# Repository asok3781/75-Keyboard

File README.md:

# Asok75
A 75% keyboard PCB.

A simple [acrylic case](Case) has also been designed - .dxf files are in the Case folder in the repository.

This PCB is designed to work with [QMK firmware](https://github.com/asok3781/qmk_firmware/tree/asok/keyboards/asok/asok75) (firmware is in my branch of the QMK firmware in the expected location).

A [VIA definition](asok75VIAdefinition) has also been created to be able to customise the layout of the keyboard easily.

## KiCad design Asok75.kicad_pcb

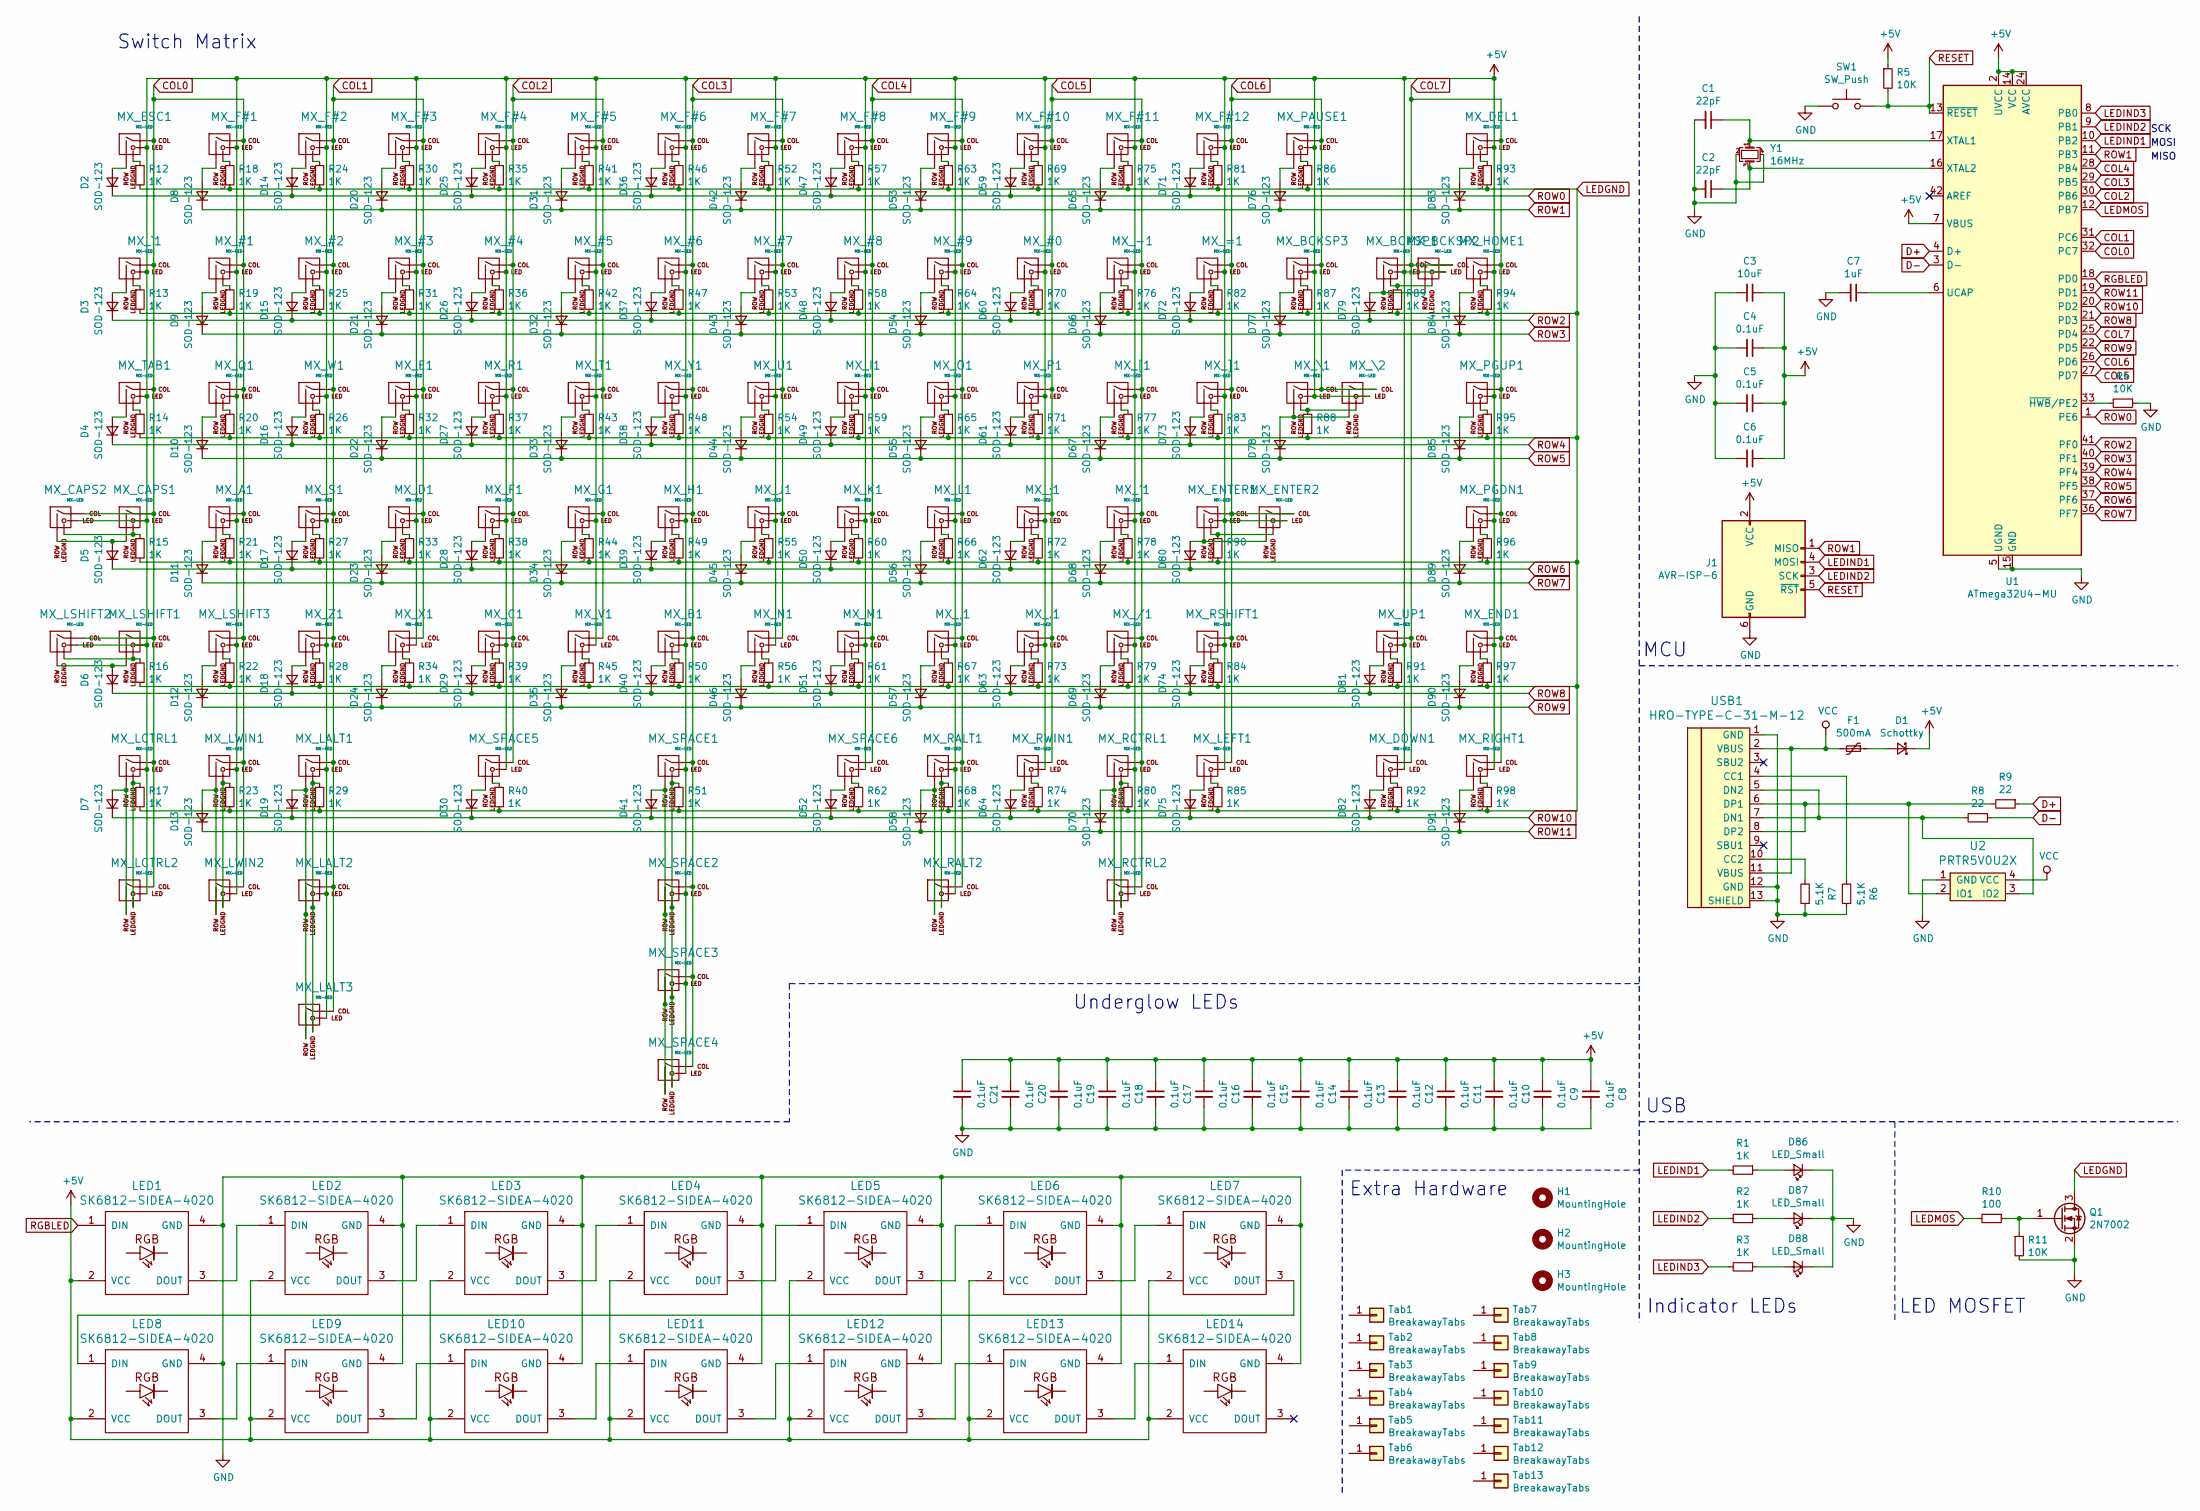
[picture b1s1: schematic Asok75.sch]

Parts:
C1, C2: 22pF; C_0805_2012Metric
C3: 10uF; C_0805_2012Metric
C4, C5, C6, C8, C9, C10, C11, C12, C13, C14, C15, C16, C17, C18, C19, C20, C21: 0.1uF; C_0805_2012Metric
C7: 1uF; C_0805_2012Metric
D1: Schottky; D_SOD-123-Pretty
D2, D3, D4, D5, D6, D7, D8, D9, D10, D11, D12, D13, D14, D15, D16, D17, D18, D19, D20, D21, D22, D23, D24, D25, D26, D27, D28, D29, D30, D31, D32, D33, D34, D35, D36, D37, D38, D39, D40, D41, D42, D43, D44, D45, D46, D47, D48, D49, D50, D51, D52, D53, D54, D55, D56, D57, D58, D59, D60, D61, D62, D63, D64, D65, D66, D67, D68, D69, D70, D71, D72, D73, D74, D75, D76, D77, D78, D79, D80, D81, D82, D83, D84, D85, D89, D90, D91: SOD-123; D_SOD-123-Pretty
D86, D87, D88: LED_Small; LED_D3.0mm-Pretty
F1: 500mA; Fuse_1206_3216Metric
H1, H2, H3: MountingHole; mounting
J1: AVR-ISP-6; Reset_Pretty-Mask
LED1, LED2, LED3, LED4, LED5, LED6, LED7, LED8, LED9, LED10, LED11, LED12, LED13, LED14: SK6812-SIDEA-4020
MX_#0, MX_#1, MX_#2, MX_#3, MX_#4, MX_#5, MX_#6, MX_#7, MX_#8, MX_#9: MX-LED; MXOnly-1U
MX_'1: MX-LED; MXOnly-1U
MX_,1: MX-LED; MXOnly-1U
MX_-1: MX-LED; MXOnly-1U
MX_.1: MX-LED; MXOnly-1U
MX_/1: MX-LED; MXOnly-1U
MX_;1: MX-LED; MXOnly-1U
MX_=1: MX-LED; MXOnly-1U
MX_A1: MX-LED; MXOnly-1U
MX_B1: MX-LED; MXOnly-1U
MX_BCKSP1: MX-LED; MXOnly-2U
MX_BCKSP2, MX_BCKSP3: MX-LED; MXOnly-1U
MX_C1: MX-LED; MXOnly-1U
MX_CAPS1: MX-LED; MXOnly-1.75U
MX_CAPS2: MX-LED; MXOnly-1.25U
MX_D1: MX-LED; MXOnly-1U
MX_DEL1: MX-LED; MXOnly-1U
MX_DOWN1: MX-LED; MXOnly-1U
MX_E1: MX-LED; MXOnly-1U
MX_END1: MX-LED; MXOnly-1U
MX_ENTER1: MX-LED; MXOnly-2.25U-ReversedStabilizers
MX_ENTER2: MX-LED; MXOnly-ISO-ROTATED-ReversedStabilizers
MX_ESC1: MX-LED; MXOnly-1U
MX_F1: MX-LED; MXOnly-1U
MX_F#1, MX_F#2, MX_F#3, MX_F#4, MX_F#5, MX_F#6, MX_F#7, MX_F#8, MX_F#9, MX_F#10, MX_F#11, MX_F#12: MX-LED; MXOnly-1U
MX_G1: MX-LED; MXOnly-1U
MX_H1: MX-LED; MXOnly-1U
MX_HOME1: MX-LED; MXOnly-1U
MX_I1: MX-LED; MXOnly-1U
MX_J1: MX-LED; MXOnly-1U
MX_K1: MX-LED; MXOnly-1U
MX_L1: MX-LED; MXOnly-1U
MX_LALT1: MX-LED; MXOnly-1.25U
MX_LALT2: MX-LED; MXOnly-1.5U-FLIPPED
MX_LALT3: MX-LED; MXOnly-1.5U
MX_LCTRL1: MX-LED; MXOnly-1.25U
MX_LCTRL2: MX-LED; MXOnly-1.5U-FLIPPED
MX_LEFT1: MX-LED; MXOnly-1U
MX_LSHIFT1: MX-LED; MXOnly-2.25U
MX_LSHIFT2: MX-LED; MXOnly-1.25U
MX_LSHIFT3: MX-LED; MXOnly-1U
MX_LWIN1: MX-LED; MXOnly-1.25U
MX_LWIN2: MX-LED; MXOnly-1U-FLIPPED
MX_M1: MX-LED; MXOnly-1U
MX_N1: MX-LED; MXOnly-1U
MX_O1: MX-LED; MXOnly-1U
MX_P1: MX-LED; MXOnly-1U
MX_PAUSE1: MX-LED; MXOnly-1U
MX_PGDN1: MX-LED; MXOnly-1U
MX_PGUP1: MX-LED; MXOnly-1U
MX_Q1: MX-LED; MXOnly-1U
MX_R1: MX-LED; MXOnly-1U
MX_RALT1: MX-LED; MXOnly-1U
MX_RALT2: MX-LED; MXOnly-1.5U
MX_RCTRL1: MX-LED; MXOnly-1U
MX_RCTRL2: MX-LED; MXOnly-1.5U
MX_RIGHT1: MX-LED; MXOnly-1U
MX_RSHIFT1: MX-LED; MXOnly-1.75U
MX_RWIN1: MX-LED; MXOnly-1U
MX_S1: MX-LED; MXOnly-1U
MX_SPACE1: MX-LED; MXOnly-6.25U-ReversedStabilizers
MX_SPACE2, MX_SPACE3: MX-LED; MXOnly-7U-ReversedStabilizers
MX_SPACE4: MX-LED; MXOnly-1.25U
MX_SPACE5: MX-LED; MXOnly-2.75U-ReversedStabilizers
MX_SPACE6: MX-LED; MXOnly-2.25U-ReversedStabilizers
MX_T1: MX-LED; MXOnly-1U
MX_TAB1: MX-LED; MXOnly-1.5U
MX_U1: MX-LED; MXOnly-1U
MX_UP1: MX-LED; MXOnly-1U
MX_V1: MX-LED; MXOnly-1U
MX_W1: MX-LED; MXOnly-1U
MX_X1: MX-LED; MXOnly-1U
MX_Y1: MX-LED; MXOnly-1U
MX_Z1: MX-LED; MXOnly-1U
MX_[1: MX-LED; MXOnly-1U
MX_\1: MX-LED; MXOnly-1.5U
MX_\2: MX-LED; MXOnly-1U
MX_]1: MX-LED; MXOnly-1U
MX_`1: MX-LED; MXOnly-1U
Q1: 2N7002; SOT-23
R1, R2, R3, R12, R13, R14, R15, R16, R17, R18, R19, R20, R21, R22, R23, R24, R25, R26, R27, R28, R29, R30, R31, R32, R33, R34, R35, R36, R37, R38, R39, R40, R41, R42, R43, R44, R45, R46, R47, R48, R49, R50, R51, R52, R53, R54, R55, R56, R57, R58, R59, R60, R61, R62, R63, R64, R65, R66, R67, R68, R69, R70, R71, R72, R73, R74, R75, R76, R77, R78, R79, R80, R81, R82, R83, R84, R85, R86, R87, R88, R89, R90, R91, R92, R93, R94, R95, R96, R97, R98: 1K; R_0805_2012Metric
R4, R5, R11: 10K; R_0805_2012Metric
R6, R7: 5.1K; R_0805_2012Metric
R8, R9: 22; R_0805_2012Metric
R10: 100; R_0805_2012Metric
SW1: SW_Push; SKQG-1155865
Tab1, Tab2, Tab3, Tab4, Tab5, Tab6, Tab7, Tab8, Tab9, Tab10, Tab11, Tab12, Tab13: BreakawayTabs; breakaway-mousebites
U1: ATmega32U4-MU; QFN-44-1EP_7x7mm_P0.5mm_EP5.2x5.2mm
U2: PRTR5V0U2X; SOT143B
USB1: HRO-TYPE-C-31-M-12; HRO-TYPE-C-31-M-12-Assembly
Y1: 16MHz; Crystal_SMD_3225-4Pin_3.2x2.5mm

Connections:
+5V: C3.1, C4.1, C5.1, C6.1, C8.1, C9.1, C10.1, C11.1, C12.1, C13.1, C14.1, C15.1, C16.1, C17.1, C18.1, C19.1, C20.1, C21.1, D1.1 (K), J1.2 (VCC), LED1.2 (VCC), LED2.2 (VCC), LED3.2 (VCC), LED4.2 (VCC), LED5.2 (VCC), LED6.2 (VCC), LED7.2 (VCC), LED8.2 (VCC), LED9.2 (VCC), LED10.2 (VCC), LED11.2 (VCC), LED12.2 (VCC), LED13.2 (VCC), LED14.2 (VCC), MX_#0.3 (LED), MX_#1.3 (LED), MX_#2.3 (LED), MX_#3.3 (LED), MX_#4.3 (LED), MX_#5.3 (LED), MX_#6.3 (LED), MX_#7.3 (LED), MX_#8.3 (LED), MX_#9.3 (LED), MX_'1.3 (LED), MX_,1.3 (LED), MX_-1.3 (LED), MX_.1.3 (LED), MX_/1.3 (LED), MX_;1.3 (LED), MX_=1.3 (LED), MX_A1.3 (LED), MX_B1.3 (LED), MX_BCKSP1.3 (LED), MX_BCKSP2.3 (LED), MX_BCKSP3.3 (LED), MX_C1.3 (LED), MX_CAPS1.3 (LED), MX_CAPS2.3 (LED), MX_D1.3 (LED), MX_DEL1.3 (LED), MX_DOWN1.3 (LED), MX_E1.3 (LED), MX_END1.3 (LED), MX_ENTER1.3 (LED), MX_ENTER2.3 (LED), MX_ESC1.3 (LED), MX_F1.3 (LED), MX_F#1.3 (LED), MX_F#2.3 (LED), MX_F#3.3 (LED), MX_F#4.3 (LED), MX_F#5.3 (LED), MX_F#6.3 (LED), MX_F#7.3 (LED), MX_F#8.3 (LED), MX_F#9.3 (LED), MX_F#10.3 (LED), MX_F#11.3 (LED), MX_F#12.3 (LED), MX_G1.3 (LED), MX_H1.3 (LED), MX_HOME1.3 (LED), MX_I1.3 (LED), MX_J1.3 (LED), MX_K1.3 (LED), MX_L1.3 (LED), MX_LALT1.3 (LED), MX_LALT2.3 (LED), MX_LALT3.3 (LED), MX_LCTRL1.3 (LED), MX_LCTRL2.3 (LED), MX_LEFT1.3 (LED), MX_LSHIFT1.3 (LED), MX_LSHIFT2.3 (LED), MX_LSHIFT3.3 (LED), MX_LWIN1.3 (LED), MX_LWIN2.3 (LED), MX_M1.3 (LED), MX_N1.3 (LED), MX_O1.3 (LED), MX_P1.3 (LED), MX_PAUSE1.3 (LED), MX_PGDN1.3 (LED), MX_PGUP1.3 (LED), MX_Q1.3 (LED), MX_R1.3 (LED), MX_RALT1.3 (LED), MX_RALT2.3 (LED), MX_RCTRL1.3 (LED), MX_RCTRL2.3 (LED), MX_RIGHT1.3 (LED), MX_RSHIFT1.3 (LED), MX_RWIN1.3 (LED), MX_S1.3 (LED), MX_SPACE1.3 (LED), MX_SPACE2.3 (LED), MX_SPACE3.3 (LED), MX_SPACE4.3 (LED), MX_SPACE5.3 (LED), MX_SPACE6.3 (LED), MX_T1.3 (LED), MX_TAB1.3 (LED), MX_U1.3 (LED), MX_UP1.3 (LED), MX_V1.3 (LED), MX_W1.3 (LED), MX_X1.3 (LED), MX_Y1.3 (LED), MX_Z1.3 (LED), MX_[1.3 (LED), MX_\1.3 (LED), MX_\2.3 (LED), MX_]1.3 (LED), MX_`1.3 (LED), R5.1, U1.2 (UVCC), U1.7 (VBUS), U1.14 (VCC), U1.24 (AVCC), U1.34 (VCC), U1.44 (AVCC); also elsewhere on the board
COL0: MX_#1.1 (COL), MX_A1.1 (COL), MX_CAPS1.1 (COL), MX_CAPS2.1 (COL), MX_ESC1.1 (COL), MX_F#1.1 (COL), MX_LCTRL1.1 (COL), MX_LCTRL2.1 (COL), MX_LSHIFT1.1 (COL), MX_LSHIFT2.1 (COL), MX_LSHIFT3.1 (COL), MX_LWIN1.1 (COL), MX_LWIN2.1 (COL), MX_Q1.1 (COL), MX_TAB1.1 (COL), MX_`1.1 (COL), U1.32 (PC7)
COL1: MX_#2.1 (COL), MX_#3.1 (COL), MX_D1.1 (COL), MX_E1.1 (COL), MX_F#2.1 (COL), MX_F#3.1 (COL), MX_LALT1.1 (COL), MX_LALT2.1 (COL), MX_LALT3.1 (COL), MX_S1.1 (COL), MX_W1.1 (COL), MX_X1.1 (COL), MX_Z1.1 (COL), U1.31 (PC6)
COL2: MX_#4.1 (COL), MX_#5.1 (COL), MX_C1.1 (COL), MX_F1.1 (COL), MX_F#4.1 (COL), MX_F#5.1 (COL), MX_G1.1 (COL), MX_R1.1 (COL), MX_SPACE5.1 (COL), MX_T1.1 (COL), MX_V1.1 (COL), U1.30 (PB6)
COL3: MX_#6.1 (COL), MX_#7.1 (COL), MX_B1.1 (COL), MX_F#6.1 (COL), MX_F#7.1 (COL), MX_H1.1 (COL), MX_J1.1 (COL), MX_N1.1 (COL), MX_SPACE1.1 (COL), MX_SPACE2.1 (COL), MX_SPACE3.1 (COL), MX_SPACE4.1 (COL), MX_U1.1 (COL), MX_Y1.1 (COL), U1.29 (PB5)
COL4: MX_#8.1 (COL), MX_#9.1 (COL), MX_,1.1 (COL), MX_F#8.1 (COL), MX_F#9.1 (COL), MX_I1.1 (COL), MX_K1.1 (COL), MX_L1.1 (COL), MX_M1.1 (COL), MX_O1.1 (COL), MX_RALT1.1 (COL), MX_RALT2.1 (COL), MX_SPACE6.1 (COL), U1.28 (PB4)
COL5: MX_#0.1 (COL), MX_'1.1 (COL), MX_-1.1 (COL), MX_.1.1 (COL), MX_/1.1 (COL), MX_;1.1 (COL), MX_F#10.1 (COL), MX_F#11.1 (COL), MX_P1.1 (COL), MX_RCTRL1.1 (COL), MX_RCTRL2.1 (COL), MX_RWIN1.1 (COL), MX_[1.1 (COL), U1.27 (PD7)
COL6: MX_=1.1 (COL), MX_BCKSP3.1 (COL), MX_ENTER1.1 (COL), MX_ENTER2.1 (COL), MX_F#12.1 (COL), MX_LEFT1.1 (COL), MX_PAUSE1.1 (COL), MX_RSHIFT1.1 (COL), MX_\1.1 (COL), MX_\2.1 (COL), MX_]1.1 (COL), U1.26 (PD6)
COL7: MX_BCKSP1.1 (COL), MX_BCKSP2.1 (COL), MX_DEL1.1 (COL), MX_DOWN1.1 (COL), MX_END1.1 (COL), MX_HOME1.1 (COL), MX_PGDN1.1 (COL), MX_PGUP1.1 (COL), MX_RIGHT1.1 (COL), MX_UP1.1 (COL), U1.25 (PD4)
D+: R9.1, U1.4 (D+)
D-: R8.1, U1.3 (D-)
GND: C1.2, C2.2, C3.2, C4.2, C5.2, C6.2, C7.2, C8.2, C9.2, C10.2, C11.2, C12.2, C13.2, C14.2, C15.2, C16.2, C17.2, C18.2, C19.2, C20.2, C21.2, D86.1 (K), D87.1 (K), D88.1 (K), J1.6 (GND), LED1.4 (GND), LED2.4 (GND), LED3.4 (GND), LED4.4 (GND), LED5.4 (GND), LED6.4 (GND), LED7.4 (GND), LED8.4 (GND), LED9.4 (GND), LED10.4 (GND), LED11.4 (GND), LED12.4 (GND), LED13.4 (GND), LED14.4 (GND), Q1.2 (S), R4.1, R6.1, R7.1, R11.2, SW1.1, U1.5 (UGND), U1.15 (GND), U1.23 (GND), U1.35 (GND), U1.43 (GND), U1.45 (GND), U2.1 (GND), USB1.1 (GND), USB1.12 (GND), USB1.13 (SHIELD), Y1.2, Y1.4; also elsewhere on the board
LEDGND: Q1.3 (D), R12.2, R13.2, R14.2, R15.2, R16.2, R17.2, R18.2, R19.2, R20.2, R21.2, R22.2, R23.2, R24.2, R25.2, R26.2, R27.2, R28.2, R29.2, R30.2, R31.2, R32.2, R33.2, R34.2, R35.2, R36.2, R37.2, R38.2, R39.2, R40.2, R41.2, R42.2, R43.2, R44.2, R45.2, R46.2, R47.2, R48.2, R49.2, R50.2, R51.2, R52.2, R53.2, R54.2, R55.2, R56.2, R57.2, R58.2, R59.2, R60.2, R61.2, R62.2, R63.2, R64.2, R65.2, R66.2, R67.2, R68.2, R69.2, R70.2, R71.2, R72.2, R73.2, R74.2, R75.2, R76.2, R77.2, R78.2, R79.2, R80.2, R81.2, R82.2, R83.2, R84.2, R85.2, R86.2, R87.2, R88.2, R89.2, R90.2, R91.2, R92.2, R93.2, R94.2, R95.2, R96.2, R97.2, R98.2
LEDIND1: J1.4 (MOSI), R1.2, U1.10 (PB2)
LEDIND2: J1.3 (SCK), R2.2, U1.9 (PB1)
LEDIND3: R3.2, U1.8 (PB0)
LEDMOS: R10.2, U1.12 (PB7)
unnamed: C1.1, U1.17 (XTAL1), Y1.1
unnamed: C2.1, U1.16 (XTAL2), Y1.3
unnamed: C7.1, U1.6 (UCAP)
unnamed: D1.2 (A), F1.1
unnamed: D2.2 (A), MX_ESC1.2 (ROW)
unnamed: D3.2 (A), MX_`1.2 (ROW)
unnamed: D4.2 (A), MX_TAB1.2 (ROW)
unnamed: D5.2 (A), MX_CAPS1.2 (ROW), MX_CAPS2.2 (ROW)
unnamed: D6.2 (A), MX_LSHIFT1.2 (ROW), MX_LSHIFT2.2 (ROW)
unnamed: D7.2 (A), MX_LCTRL1.2 (ROW), MX_LCTRL2.2 (ROW)
unnamed: D8.2 (A), MX_F#1.2 (ROW)
unnamed: D9.2 (A), MX_#1.2 (ROW)
unnamed: D10.2 (A), MX_Q1.2 (ROW)
unnamed: D11.2 (A), MX_A1.2 (ROW)
unnamed: D12.2 (A), MX_LSHIFT3.2 (ROW)
unnamed: D13.2 (A), MX_LWIN1.2 (ROW), MX_LWIN2.2 (ROW)
unnamed: D14.2 (A), MX_F#2.2 (ROW)
unnamed: D15.2 (A), MX_#2.2 (ROW)
unnamed: D16.2 (A), MX_W1.2 (ROW)
unnamed: D17.2 (A), MX_S1.2 (ROW)
unnamed: D18.2 (A), MX_Z1.2 (ROW)
unnamed: D19.2 (A), MX_LALT1.2 (ROW), MX_LALT2.2 (ROW), MX_LALT3.2 (ROW)
unnamed: D20.2 (A), MX_F#3.2 (ROW)
unnamed: D21.2 (A), MX_#3.2 (ROW)
unnamed: D22.2 (A), MX_E1.2 (ROW)
unnamed: D23.2 (A), MX_D1.2 (ROW)
unnamed: D24.2 (A), MX_X1.2 (ROW)
unnamed: D25.2 (A), MX_F#4.2 (ROW)
unnamed: D26.2 (A), MX_#4.2 (ROW)
unnamed: D27.2 (A), MX_R1.2 (ROW)
unnamed: D28.2 (A), MX_F1.2 (ROW)
unnamed: D29.2 (A), MX_C1.2 (ROW)
unnamed: D30.2 (A), MX_SPACE5.2 (ROW)
unnamed: D31.2 (A), MX_F#5.2 (ROW)
unnamed: D32.2 (A), MX_#5.2 (ROW)
unnamed: D33.2 (A), MX_T1.2 (ROW)
unnamed: D34.2 (A), MX_G1.2 (ROW)
unnamed: D35.2 (A), MX_V1.2 (ROW)
unnamed: D36.2 (A), MX_F#6.2 (ROW)
unnamed: D37.2 (A), MX_#6.2 (ROW)
unnamed: D38.2 (A), MX_Y1.2 (ROW)
unnamed: D39.2 (A), MX_H1.2 (ROW)
unnamed: D40.2 (A), MX_B1.2 (ROW)
unnamed: D41.2 (A), MX_SPACE1.2 (ROW), MX_SPACE2.2 (ROW), MX_SPACE3.2 (ROW), MX_SPACE4.2 (ROW)
unnamed: D42.2 (A), MX_F#7.2 (ROW)
unnamed: D43.2 (A), MX_#7.2 (ROW)
unnamed: D44.2 (A), MX_U1.2 (ROW)
unnamed: D45.2 (A), MX_J1.2 (ROW)
unnamed: D46.2 (A), MX_N1.2 (ROW)
unnamed: D47.2 (A), MX_F#8.2 (ROW)
unnamed: D48.2 (A), MX_#8.2 (ROW)
unnamed: D49.2 (A), MX_I1.2 (ROW)
unnamed: D50.2 (A), MX_K1.2 (ROW)
unnamed: D51.2 (A), MX_M1.2 (ROW)
unnamed: D52.2 (A), MX_SPACE6.2 (ROW)
unnamed: D53.2 (A), MX_F#9.2 (ROW)
unnamed: D54.2 (A), MX_#9.2 (ROW)
unnamed: D55.2 (A), MX_O1.2 (ROW)
unnamed: D56.2 (A), MX_L1.2 (ROW)
unnamed: D57.2 (A), MX_,1.2 (ROW)
unnamed: D58.2 (A), MX_RALT1.2 (ROW), MX_RALT2.2 (ROW)
unnamed: D59.2 (A), MX_F#10.2 (ROW)
unnamed: D60.2 (A), MX_#0.2 (ROW)
unnamed: D61.2 (A), MX_P1.2 (ROW)
unnamed: D62.2 (A), MX_;1.2 (ROW)
unnamed: D63.2 (A), MX_.1.2 (ROW)
unnamed: D64.2 (A), MX_RWIN1.2 (ROW)
unnamed: D65.2 (A), MX_F#11.2 (ROW)
unnamed: D66.2 (A), MX_-1.2 (ROW)
unnamed: D67.2 (A), MX_[1.2 (ROW)
unnamed: D68.2 (A), MX_'1.2 (ROW)
unnamed: D69.2 (A), MX_/1.2 (ROW)
unnamed: D70.2 (A), MX_RCTRL1.2 (ROW), MX_RCTRL2.2 (ROW)
unnamed: D71.2 (A), MX_F#12.2 (ROW)
unnamed: D72.2 (A), MX_=1.2 (ROW)
unnamed: D73.2 (A), MX_]1.2 (ROW)
unnamed: D74.2 (A), MX_RSHIFT1.2 (ROW)
unnamed: D75.2 (A), MX_LEFT1.2 (ROW)
unnamed: D76.2 (A), MX_PAUSE1.2 (ROW)
unnamed: D77.2 (A), MX_BCKSP3.2 (ROW)
unnamed: D78.2 (A), MX_\1.2 (ROW), MX_\2.2 (ROW)
unnamed: D79.2 (A), MX_BCKSP1.2 (ROW), MX_BCKSP2.2 (ROW)
unnamed: D80.2 (A), MX_ENTER1.2 (ROW), MX_ENTER2.2 (ROW)
unnamed: D81.2 (A), MX_UP1.2 (ROW)
unnamed: D82.2 (A), MX_DOWN1.2 (ROW)
unnamed: D83.2 (A), MX_DEL1.2 (ROW)
unnamed: D84.2 (A), MX_HOME1.2 (ROW)
unnamed: D85.2 (A), MX_PGUP1.2 (ROW)
unnamed: D86.2 (A), R1.1
unnamed: D87.2 (A), R2.1
unnamed: D88.2 (A), R3.1
unnamed: D89.2 (A), MX_PGDN1.2 (ROW)
unnamed: D90.2 (A), MX_END1.2 (ROW)
unnamed: D91.2 (A), MX_RIGHT1.2 (ROW)
unnamed: LED1.3 (DOUT), LED2.1 (DIN)
unnamed: LED2.3 (DOUT), LED3.1 (DIN)
unnamed: LED3.3 (DOUT), LED4.1 (DIN)
unnamed: LED4.3 (DOUT), LED5.1 (DIN)
unnamed: LED5.3 (DOUT), LED6.1 (DIN)
unnamed: LED6.3 (DOUT), LED7.1 (DIN)
unnamed: LED7.3 (DOUT), LED8.1 (DIN)
unnamed: LED8.3 (DOUT), LED9.1 (DIN)
unnamed: LED9.3 (DOUT), LED10.1 (DIN)
unnamed: LED10.3 (DOUT), LED11.1 (DIN)
unnamed: LED11.3 (DOUT), LED12.1 (DIN)
unnamed: LED12.3 (DOUT), LED13.1 (DIN)
unnamed: LED13.3 (DOUT), LED14.1 (DIN)
unnamed: MX_#0.4 (LEDGND), R70.1
unnamed: MX_#1.4 (LEDGND), R19.1
unnamed: MX_#2.4 (LEDGND), R25.1
unnamed: MX_#3.4 (LEDGND), R31.1
unnamed: MX_#4.4 (LEDGND), R36.1
unnamed: MX_#5.4 (LEDGND), R42.1
unnamed: MX_#6.4 (LEDGND), R47.1
unnamed: MX_#7.4 (LEDGND), R53.1
unnamed: MX_#8.4 (LEDGND), R58.1
unnamed: MX_#9.4 (LEDGND), R64.1
unnamed: MX_'1.4 (LEDGND), R78.1
unnamed: MX_,1.4 (LEDGND), R67.1
unnamed: MX_-1.4 (LEDGND), R76.1
unnamed: MX_.1.4 (LEDGND), R73.1
unnamed: MX_/1.4 (LEDGND), R79.1
unnamed: MX_;1.4 (LEDGND), R72.1
unnamed: MX_=1.4 (LEDGND), R82.1
unnamed: MX_A1.4 (LEDGND), R21.1
unnamed: MX_B1.4 (LEDGND), R50.1
unnamed: MX_BCKSP1.4 (LEDGND), MX_BCKSP2.4 (LEDGND), R89.1
unnamed: MX_BCKSP3.4 (LEDGND), R87.1
unnamed: MX_C1.4 (LEDGND), R39.1
unnamed: MX_CAPS1.4 (LEDGND), MX_CAPS2.4 (LEDGND), R15.1
unnamed: MX_D1.4 (LEDGND), R33.1
unnamed: MX_DEL1.4 (LEDGND), R93.1
unnamed: MX_DOWN1.4 (LEDGND), R92.1
unnamed: MX_E1.4 (LEDGND), R32.1
unnamed: MX_END1.4 (LEDGND), R97.1
unnamed: MX_ENTER1.4 (LEDGND), MX_ENTER2.4 (LEDGND), R90.1
unnamed: MX_ESC1.4 (LEDGND), R12.1
unnamed: MX_F1.4 (LEDGND), R38.1
unnamed: MX_F#1.4 (LEDGND), R18.1
unnamed: MX_F#2.4 (LEDGND), R24.1
unnamed: MX_F#3.4 (LEDGND), R30.1
unnamed: MX_F#4.4 (LEDGND), R35.1
unnamed: MX_F#5.4 (LEDGND), R41.1
unnamed: MX_F#6.4 (LEDGND), R46.1
unnamed: MX_F#7.4 (LEDGND), R52.1
unnamed: MX_F#8.4 (LEDGND), R57.1
unnamed: MX_F#9.4 (LEDGND), R63.1
unnamed: MX_F#10.4 (LEDGND), R69.1
unnamed: MX_F#11.4 (LEDGND), R75.1
unnamed: MX_F#12.4 (LEDGND), R81.1
unnamed: MX_G1.4 (LEDGND), R44.1
unnamed: MX_H1.4 (LEDGND), R49.1
unnamed: MX_HOME1.4 (LEDGND), R94.1
unnamed: MX_I1.4 (LEDGND), R59.1
unnamed: MX_J1.4 (LEDGND), R55.1
unnamed: MX_K1.4 (LEDGND), R60.1
unnamed: MX_L1.4 (LEDGND), R66.1
unnamed: MX_LALT1.4 (LEDGND), MX_LALT2.4 (LEDGND), MX_LALT3.4 (LEDGND), R29.1
unnamed: MX_LCTRL1.4 (LEDGND), MX_LCTRL2.4 (LEDGND), R17.1
unnamed: MX_LEFT1.4 (LEDGND), R85.1
unnamed: MX_LSHIFT1.4 (LEDGND), MX_LSHIFT2.4 (LEDGND), R16.1
unnamed: MX_LSHIFT3.4 (LEDGND), R22.1
unnamed: MX_LWIN1.4 (LEDGND), MX_LWIN2.4 (LEDGND), R23.1
unnamed: MX_M1.4 (LEDGND), R61.1
unnamed: MX_N1.4 (LEDGND), R56.1
unnamed: MX_O1.4 (LEDGND), R65.1
unnamed: MX_P1.4 (LEDGND), R71.1
unnamed: MX_PAUSE1.4 (LEDGND), R86.1
unnamed: MX_PGDN1.4 (LEDGND), R96.1
unnamed: MX_PGUP1.4 (LEDGND), R95.1
unnamed: MX_Q1.4 (LEDGND), R20.1
unnamed: MX_R1.4 (LEDGND), R37.1
unnamed: MX_RALT1.4 (LEDGND), MX_RALT2.4 (LEDGND), R68.1
unnamed: MX_RCTRL1.4 (LEDGND), MX_RCTRL2.4 (LEDGND), R80.1
unnamed: MX_RIGHT1.4 (LEDGND), R98.1
unnamed: MX_RSHIFT1.4 (LEDGND), R84.1
unnamed: MX_RWIN1.4 (LEDGND), R74.1
unnamed: MX_S1.4 (LEDGND), R27.1
unnamed: MX_SPACE1.4 (LEDGND), MX_SPACE2.4 (LEDGND), MX_SPACE3.4 (LEDGND), MX_SPACE4.4 (LEDGND), R51.1
unnamed: MX_SPACE5.4 (LEDGND), R40.1
unnamed: MX_SPACE6.4 (LEDGND), R62.1
unnamed: MX_T1.4 (LEDGND), R43.1
unnamed: MX_TAB1.4 (LEDGND), R14.1
unnamed: MX_U1.4 (LEDGND), R54.1
unnamed: MX_UP1.4 (LEDGND), R91.1
unnamed: MX_V1.4 (LEDGND), R45.1
unnamed: MX_W1.4 (LEDGND), R26.1
unnamed: MX_X1.4 (LEDGND), R34.1
unnamed: MX_Y1.4 (LEDGND), R48.1
unnamed: MX_Z1.4 (LEDGND), R28.1
unnamed: MX_[1.4 (LEDGND), R77.1
unnamed: MX_\1.4 (LEDGND), MX_\2.4 (LEDGND), R88.1
unnamed: MX_]1.4 (LEDGND), R83.1
unnamed: MX_`1.4 (LEDGND), R13.1
unnamed: Q1.1 (G), R10.1, R11.1
unnamed: R4.2, U1.33 (~HWB~/PE2)
unnamed: R6.2, USB1.4 (CC1)
unnamed: R7.2, USB1.10 (CC2)
unnamed: R8.2, U2.3 (IO2), USB1.5 (DN2), USB1.7 (DN1)
unnamed: R9.2, U2.2 (IO1), USB1.6 (DP1), USB1.8 (DP2)
RESET: J1.5 (~RST), R5.2, SW1.2, U1.13 (~RESET)
RGBLED: LED1.1 (DIN), U1.18 (PD0); also elsewhere on the board
ROW0: D2.1 (K), D14.1 (K), D25.1 (K), D36.1 (K), D47.1 (K), D59.1 (K), D71.1 (K), U1.1 (PE6)
ROW1: D8.1 (K), D20.1 (K), D31.1 (K), D42.1 (K), D53.1 (K), D65.1 (K), D76.1 (K), D83.1 (K), J1.1 (MISO), U1.11 (PB3)
ROW2: D3.1 (K), D15.1 (K), D26.1 (K), D37.1 (K), D48.1 (K), D60.1 (K), D72.1 (K), D79.1 (K), U1.41 (PF0)
ROW3: D9.1 (K), D21.1 (K), D32.1 (K), D43.1 (K), D54.1 (K), D66.1 (K), D77.1 (K), D84.1 (K), U1.40 (PF1)
ROW4: D4.1 (K), D16.1 (K), D27.1 (K), D38.1 (K), D49.1 (K), D61.1 (K), D73.1 (K), U1.39 (PF4)
ROW5: D10.1 (K), D22.1 (K), D33.1 (K), D44.1 (K), D55.1 (K), D67.1 (K), D78.1 (K), D85.1 (K), U1.38 (PF5)
ROW6: D5.1 (K), D17.1 (K), D28.1 (K), D39.1 (K), D50.1 (K), D62.1 (K), D80.1 (K), U1.37 (PF6)
ROW7: D11.1 (K), D23.1 (K), D34.1 (K), D45.1 (K), D56.1 (K), D68.1 (K), D89.1 (K), U1.36 (PF7)
ROW8: D6.1 (K), D18.1 (K), D29.1 (K), D40.1 (K), D51.1 (K), D63.1 (K), D74.1 (K), D81.1 (K), U1.21 (PD3)
ROW9: D12.1 (K), D24.1 (K), D35.1 (K), D46.1 (K), D57.1 (K), D69.1 (K), D90.1 (K), U1.22 (PD5)
ROW10: D7.1 (K), D19.1 (K), D30.1 (K), D41.1 (K), D52.1 (K), D64.1 (K), D75.1 (K), D82.1 (K), U1.20 (PD2)
ROW11: D13.1 (K), D58.1 (K), D70.1 (K), D91.1 (K), U1.19 (PD1)
VCC: F1.2, U2.4 (VCC), USB1.2 (VBUS), USB1.11 (VBUS)

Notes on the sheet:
MCU
USB
Indicator LEDs
Switch Matrix
LED MOSFET
Underglow LEDs
SCK
MOSI
MISO
Extra Hardware

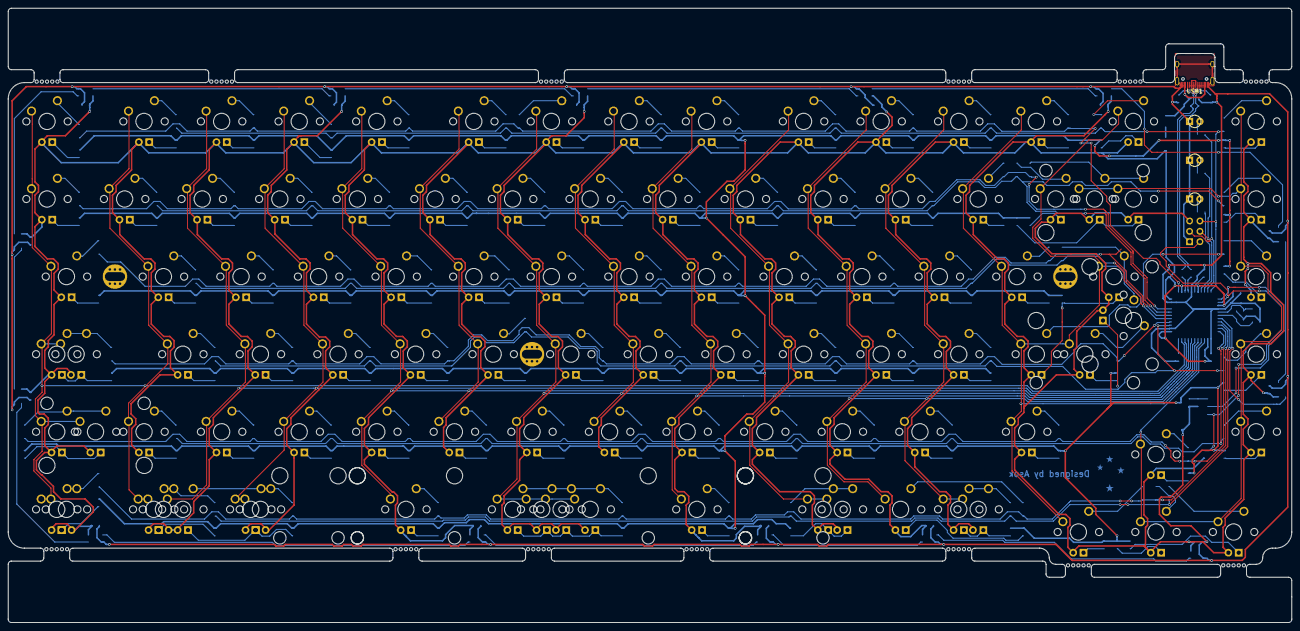
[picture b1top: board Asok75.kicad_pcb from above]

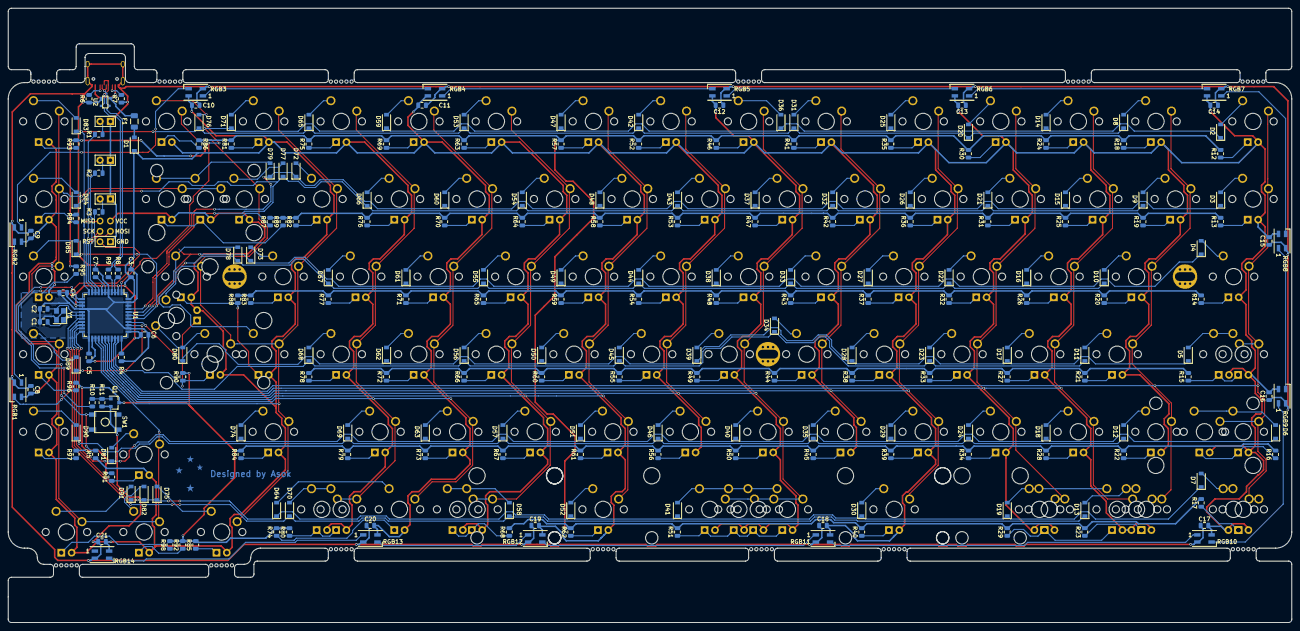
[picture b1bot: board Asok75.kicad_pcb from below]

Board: 2 copper layers, 315.1 x 150.8 mm, 349 parts (228 on the bottom side), 232 nets.

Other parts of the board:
RGB1, RGB2, RGB3, RGB4, RGB5, RGB6, RGB7, RGB8, RGB9, RGB10, RGB11, RGB12, RGB13, RGB14: SK6812MINI; LED_SK6812MINI_PLCC4_3.5x3.5mm_P1.75mm

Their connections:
+5V: RGB1.4, RGB2.4, RGB3.4, RGB4.4, RGB5.4, RGB6.4, RGB7.4, RGB8.4, RGB9.4, RGB10.4, RGB11.4, RGB12.4, RGB13.4, RGB14.4; also elsewhere on the board
GND: RGB1.2, RGB2.2, RGB3.2, RGB4.2, RGB5.2, RGB6.2, RGB7.2, RGB8.2, RGB9.2, RGB10.2, RGB11.2, RGB12.2, RGB13.2, RGB14.2; also elsewhere on the board
unnamed: RGB1.1, RGB2.3
unnamed: RGB2.1, RGB3.3
unnamed: RGB3.1, RGB4.3
unnamed: RGB4.1, RGB5.3
unnamed: RGB5.1, RGB6.3
unnamed: RGB6.1, RGB7.3
unnamed: RGB7.1, RGB8.3
unnamed: RGB8.1, RGB9.3
unnamed: RGB10.1, RGB11.3
unnamed: RGB9.1, RGB10.3
unnamed: RGB11.1, RGB12.3
unnamed: RGB12.1, RGB13.3
unnamed: RGB13.1, RGB14.3
RGBLED: RGB1.3; also elsewhere on the board
